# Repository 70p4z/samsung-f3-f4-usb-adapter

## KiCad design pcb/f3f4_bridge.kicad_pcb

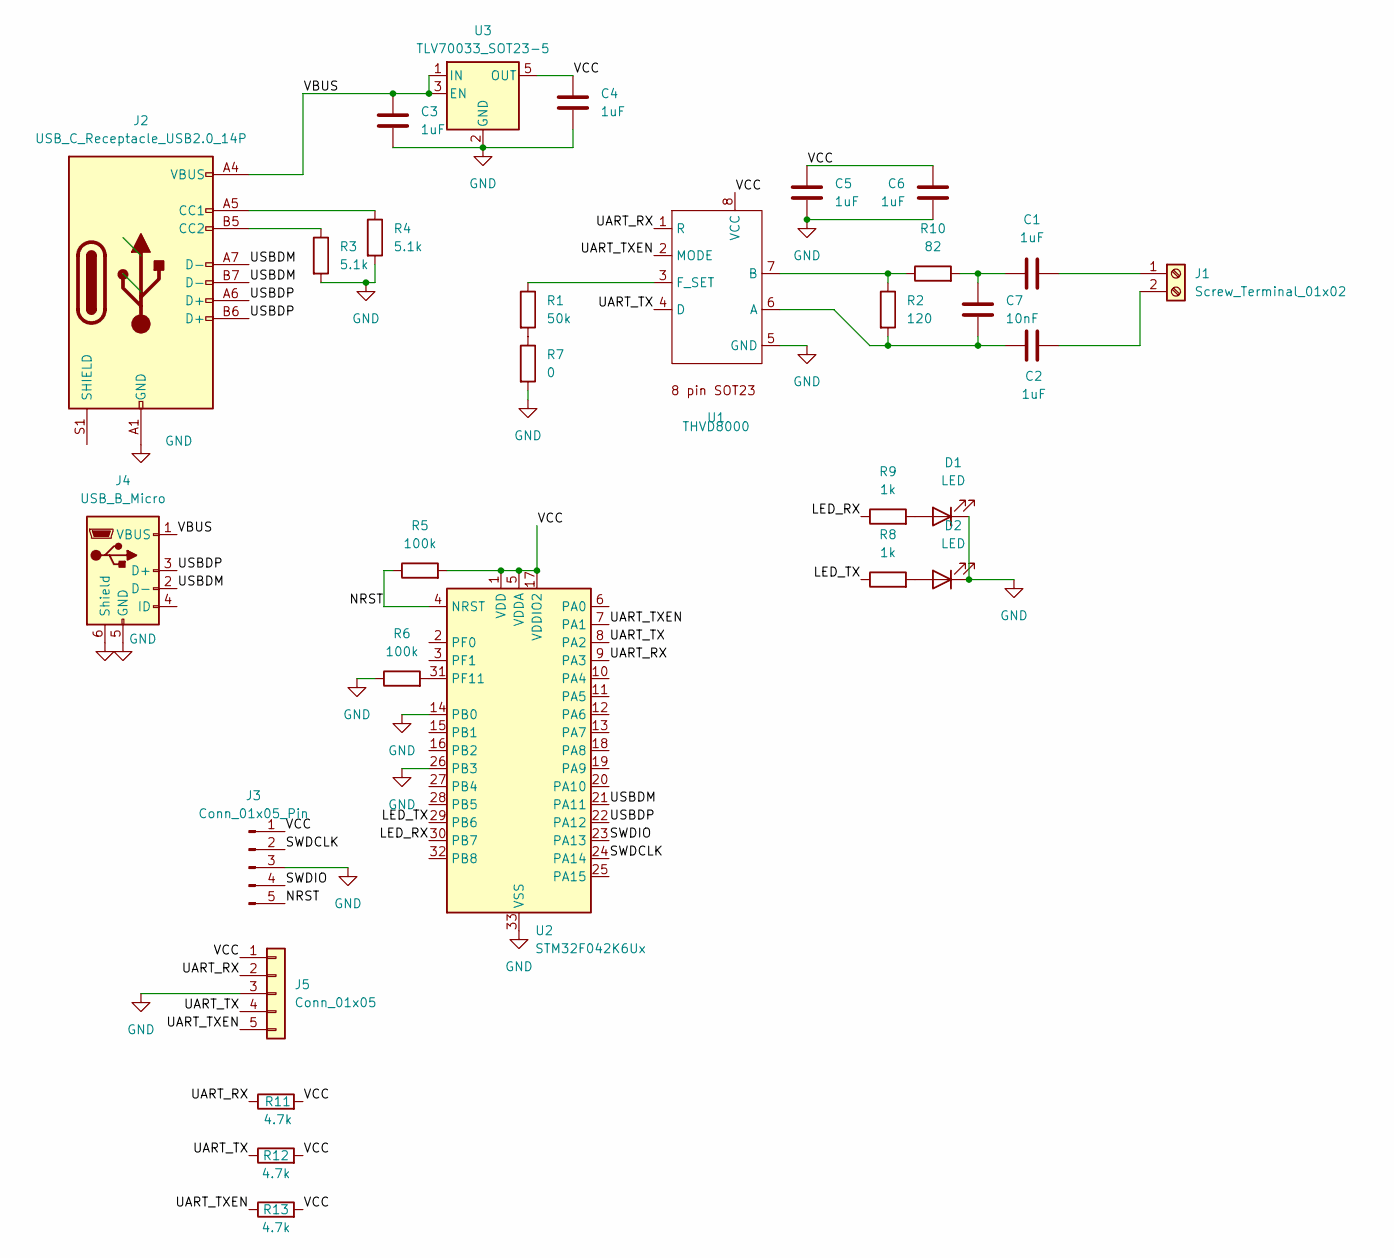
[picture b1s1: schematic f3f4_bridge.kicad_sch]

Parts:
C1, C2, C3, C4, C5, C6: 1uF; C_0603_1608Metric; LCSC C15849
C7: 10nF; C_0603_1608Metric; LCSC C57112
D1, D2: LED; LED_0603_1608Metric; LCSC C2286
J1: Screw_Terminal_01x02; TerminalBlock_bornier-2_P5.08mm; LCSC C709041
J2: USB_C_Receptacle_USB2.0_14P; USB_C_Receptacle_XKB_U262-16XN-4BVC11; LCSC C2765186
J3: Conn_01x05_Pin; PinHeader_1x05_P2.54mm_Vertical; LCSC C492404
J4: USB_B_Micro; USB_Micro-B_Wuerth_629105150521
J5: Conn_01x05; PinHeader_1x05_P2.54mm_Vertical; LCSC C492404
R1: 50k; R_0603_1608Metric; LCSC C25819
R2: 120; R_0603_1608Metric; LCSC C22787
R3, R4: 5.1k; R_0603_1608Metric; LCSC C23186
R5, R6: 100k; R_0603_1608Metric; LCSC C25803
R7: 0; R_0603_1608Metric; LCSC C4211
R8, R9: 1k; R_0603_1608Metric; LCSC C21190
R10: 82; R_0603_1608Metric; LCSC C23255
R11, R12, R13: 4.7k; R_0603_1608Metric; LCSC C23162
U1: THVD8000; SOT-23-8; LCSC C2848812
U2: STM32F042K6Ux; QFN-32-1EP_5x5mm_P0.5mm_EP3.45x3.45mm; LCSC C2053439
U3: TLV70033_SOT23-5; SOT-23-5; LCSC C5884123

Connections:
/LED_RX: R9.1, U2.30 (PB7)
/LED_TX: R8.1, U2.29 (PB6)
/NRST: J3.5, R5.1, U2.4 (NRST)
/SWDCLK: J3.2, U2.24 (PA14)
/SWDIO: J3.4, U2.23 (PA13)
/UART_RX: J5.2, R11.1, U1.1 (R), U2.9 (PA3)
/UART_TX: J5.4, R12.1, U1.4 (D), U2.8 (PA2)
/UART_TXEN: J5.5, R13.1, U1.2 (MODE), U2.7 (PA1)
/USBDM: J2.A7 (D-), J2.B7 (D-), J4.2 (D-), U2.21 (PA11)
/USBDP: J2.A6 (D+), J2.B6 (D+), J4.3 (D+), U2.22 (PA12)
/VBUS: C3.2, J2.A4 (VBUS), J2.A9 (VBUS), J2.B4 (VBUS), J2.B9 (VBUS), J4.1 (VBUS), U3.1 (IN), U3.3 (EN)
/VCC: C4.2, C5.2, C6.2, J3.1, J5.1, R5.2, R11.2, R12.2, R13.2, U1.8 (VCC), U2.1 (VDD), U2.5 (VDDA), U2.17 (VDDIO2), U3.5 (OUT)
GND: C3.1, C4.1, C5.1, C6.1, D1.1 (K), D2.1 (K), J2.A1 (GND), J2.A12 (GND), J2.B1 (GND), J2.B12 (GND), J3.3, J4.5 (GND), J4.6 (Shield), J5.3, R3.2, R4.2, R6.1, R7.2, U1.5 (GND), U2.14 (PB0), U2.26 (PB3), U2.33 (VSS), U3.2 (GND)
unnamed: C1.1, C7.2, R10.2
unnamed: D1.2 (A), R9.2
unnamed: D2.2 (A), R8.2
unnamed: C1.2, J1.1
unnamed: C2.2, J1.2
unnamed: J2.A5 (CC1), R4.1
unnamed: J2.B5 (CC2), R3.1
unnamed: R1.2, R7.1
unnamed: C2.1, C7.1, R2.2, U1.6 (A)
unnamed: R2.1, R10.1, U1.7 (B)
unnamed: R1.1, U1.3 (F_SET)
unnamed: R6.2, U2.31 (PF11)

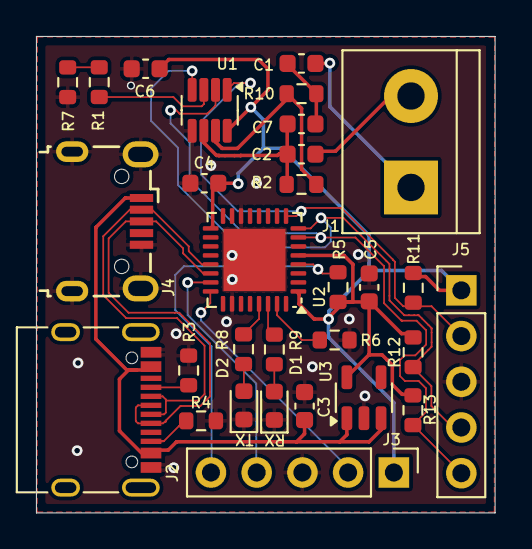
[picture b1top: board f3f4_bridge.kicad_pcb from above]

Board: 2 copper layers, 25.5 x 26.5 mm, 30 parts (0 on the bottom side), 25 nets.

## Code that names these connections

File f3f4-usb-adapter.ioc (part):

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Mcu.Name=STM32F042K(4-6)Tx
Mcu.Package=LQFP32
Mcu.UserName=STM32F042K6Tx
PA1.GPIOParameters=GPIO_Label
PA1.GPIO_Label=TXEN
PA1.Signal=GPIO_Output
PA11.Mode=Device
PA11.Signal=USB_DM
PA12.Mode=Device
PA12.Signal=USB_DP
PA13.Mode=Serial_Wire
PA13.Signal=SYS_SWDIO
PA14.Mode=Serial_Wire
PA14.Signal=SYS_SWCLK
PA2.Mode=Asynchronous
PA2.Signal=USART2_TX
PA3.Mode=Asynchronous
PA3.Signal=USART2_RX
RCC.SYSCLKFreq_VALUE=48000000
RCC.SYSCLKSource=RCC_SYSCLKSOURCE_HSI48
board=custom

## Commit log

2025-02-12 initial import
2025-02-12 first code complete import
2025-02-12 add PCB design
2025-02-12 fix serial number for windows correct enumeration
2025-02-12 add built binary for easier loading
2025-06-02 avoid hangs upon uart errors
2025-06-02 fixup descriptors with unicode troubles
2025-06-02 fix warnings
2025-06-02 prepare for external pulled usart lines, to allow for ext dupont header drive
2025-06-02 add led tx and led rx driver
2025-06-19 add back to STM32 bootloader (masserase) add rule to flash using dfu-util fix led lighting
2025-06-19 - make the state machine more robust vs usb enumeration - fix pin modes for usart and txen - fix pin pull resistor to allow external dupont header for thvd interaction
2025-06-20 fix invalid inverted rx and tx leds
2025-07-07 add nvic reset upon errors commit gerbers and a board image
2025-07-07 commit update binaries
2025-07-08 add makefile flash loading methods
2025-07-22 commit first distributed image
